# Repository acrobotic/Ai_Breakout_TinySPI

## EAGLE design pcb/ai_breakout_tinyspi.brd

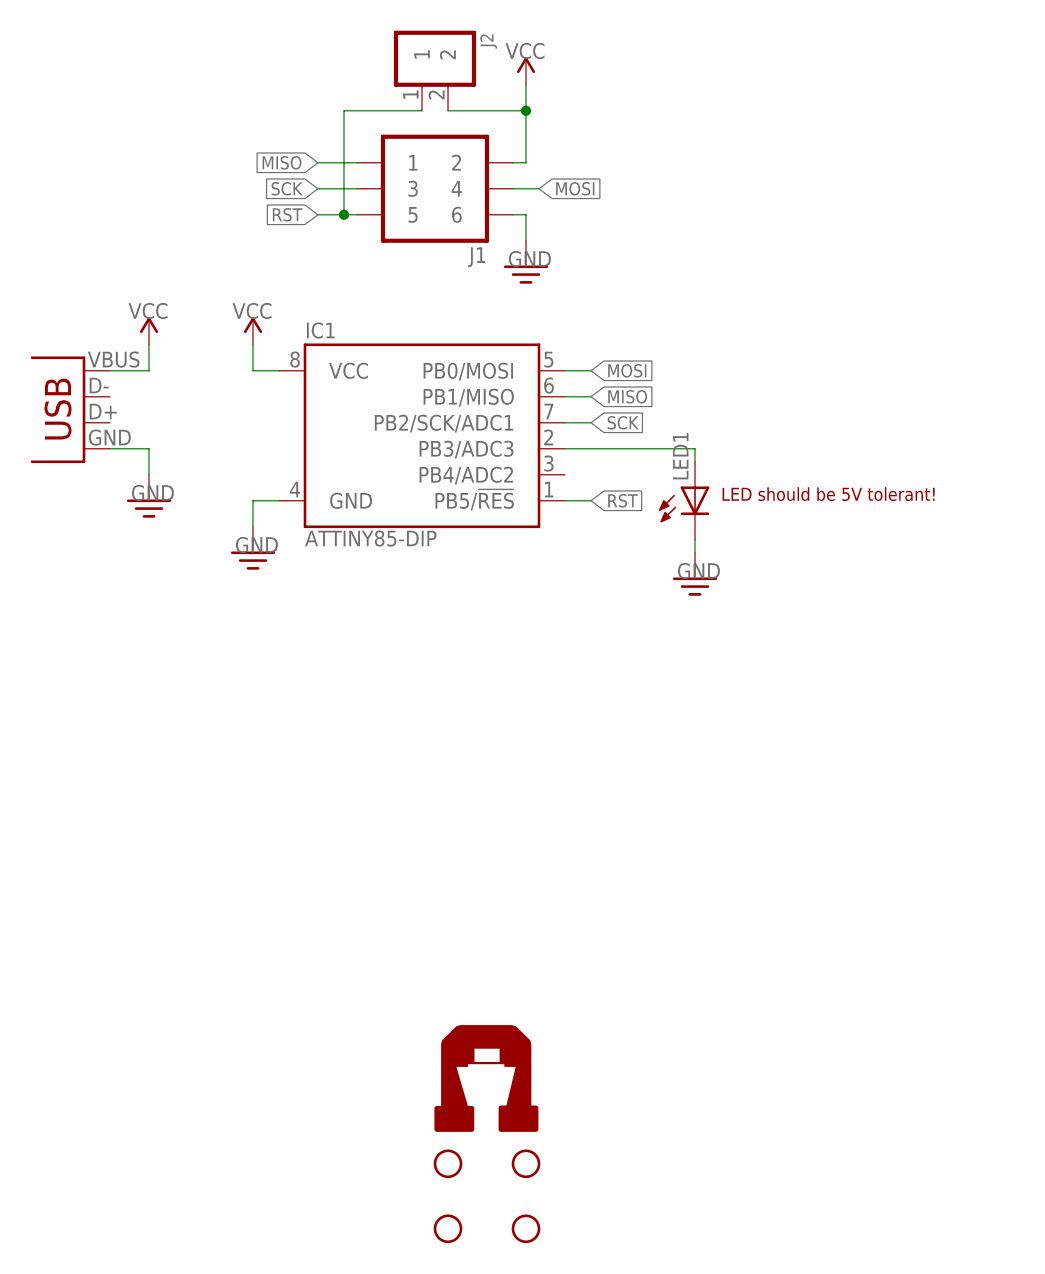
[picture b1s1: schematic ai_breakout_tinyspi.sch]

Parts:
IC1: ATTINY85-DIP; DIL08
J1: 2X03
J2: 1X02NOFIRST; 1X02-NOFIRST
LED1: LED5MM; LED-5MM
STANDOFF1, STANDOFF2, STANDOFF3, STANDOFF4: STAND-OFF
U$1: AI-LOGOXS; AI-LOGO-XS
USB1: USBMICROB-TH; USB-MICROB-TH

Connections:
GND: IC1.4 (GND), J1.6, LED1.C, USB1.GND
MISO: IC1.6 (PB1/MISO), J1.1
MOSI: IC1.5 (PB0/MOSI), J1.4
unnamed: IC1.2 (PB3/ADC3), LED1.A
RST: IC1.1 (PB5/!RES), J1.5, J2.1
SCK: IC1.7 (PB2/SCK/ADC1), J1.3
VCC: IC1.8 (VCC), J1.2, J2.2, USB1.VBUS

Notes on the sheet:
LED should be 5V tolerant!

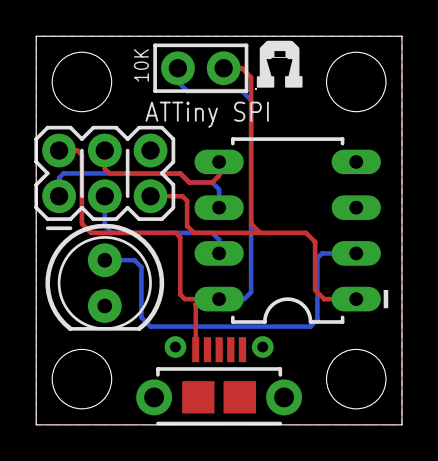
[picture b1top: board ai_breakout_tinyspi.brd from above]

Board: 2 copper layers, 20.3 x 21.6 mm, 10 parts (0 on the bottom side), 7 nets.
